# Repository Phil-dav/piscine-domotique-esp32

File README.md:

# Gestion de filtration piscine — ESP32 / Rust

Système domotique embarqué qui pilote la pompe de filtration d'une piscine
familiale : température de l'eau, sécurités matérielles, planification
automatique, tableau de bord web, suivi cloud. Écrit en Rust sur ESP32
(`esp-idf-hal` / `esp-idf-svc`), portage et évolution d'un projet
C++/PlatformIO de référence.

## Sommaire

- [Aperçu](#aperçu)
- [Fonctionnalités](#fonctionnalités)
- [Architecture matérielle](#architecture-matérielle)
- [Organisation des fichiers](#organisation-des-fichiers)
- [Démarrage](#démarrage)
- [Tableau de bord web](#tableau-de-bord-web)
- [État du projet](#état-du-projet)
- [Licence](#licence)

## Aperçu

Le montage pilote une pompe de filtration selon trois modes sélectionnables
par un interrupteur physique — **AUTO** (durée de filtration calculée selon la
température de l'eau, dans une plage horaire configurable), **MANUEL**
(marche/arrêt à la demande) et **OFF** — avec un jeu de sécurités matérielles
(niveau d'eau, défaut moteur, anti-gel, canicule) qui prennent le pas sur
n'importe quel mode en cas de besoin. Un serveur web embarqué directement sur
l'ESP32 sert un tableau de bord en temps réel, sans dépendance à un service
externe pour fonctionner au quotidien.

## Fonctionnalités

- **Trois modes de fonctionnement** (interrupteur physique 3 positions) : AUTO,
  MANUEL (bouton ou page web), OFF.
- **Sécurités matérielles** : niveau d'eau, défaut moteur (disjoncteur),
  anti-gel, canicule, anti-claquement du relais (protection contre un cyclage
  trop rapide).
- **Task Watchdog** : tout blocage de plus de 5 s de la boucle principale
  déclenche un redémarrage automatique et journalisé, plutôt qu'un blocage
  total silencieux.
- **Tableau de bord web embarqué**, servi directement par l'ESP32 : température
  eau/air, humidité, état pompe, mode, position GPS, tension batterie, timeline
  colorée des modes de la journée (avec trace réelle de la marche pompe),
  marche forcée, réglage de la plage horaire, consultation des journaux
  (sessions pompe, bilans journaliers, alertes).
- **Journalisation persistante** (NVS) : sessions pompe, bilans journaliers,
  alertes, et compteurs du jour — survivent aux redémarrages.
- **Suivi cloud** vers [Adafruit IO](https://io.adafruit.com) : envoi groupé de
  toutes les mesures en une seule requête HTTP par cycle, dans un fil
  d'exécution dédié, jamais dans la boucle principale surveillée par le
  watchdog.
- **Horodatage GPS avec repli NTP** : heure fiable même sans réseau Wi-Fi.
- **Suivi de l'alimentation batterie/solaire** (en cours de câblage) : deux
  ponts diviseurs de tension pour surveiller la batterie 12V et la sortie
  régulée 5V d'un contrôleur de charge solaire.

## Architecture matérielle

| Bus / broche | Composant | Rôle |
| --- | --- | --- |
| I2C (GPIO21 SDA, GPIO22 SCL, 400 kHz) | AHT10 (0x38) | Température / humidité air |
| I2C | PCF8574 (0x21) | Expandeur de broches (relais, boutons, interrupteur de mode) |
| I2C | SSD1306 (0x3C) | Écran OLED de diagnostic |
| 1-Wire (GPIO4) | DS18B20 | Température de l'eau |
| UART2 (GPIO16 RX) | Module GPS | Horodatage et coordonnées |
| ADC1 (GPIO34) | Détecteur de niveau | Sécurité niveau d'eau |
| ADC1 (GPIO32, GPIO35) | Ponts diviseurs | Tension batterie 12V / sortie solaire 5V |

Détail du câblage du PCF8574 : P0 pilote le relais pompe, P3 le relais de
défaut système, P4/P5/P6 lisent respectivement le bouton écran et
l'interrupteur de mode (MANU/AUTO), P7 lit le retour de défaut moteur.

Schéma KiCad complet du montage. Il inclut des blocs anticipés dans la
conception (carte micro SD, pH-mètre PH-4502C, interrupteurs de logs série)
qui sont déjà câblés mais **pas encore pris en charge par le firmware
actuel** — schéma établi en amont de la réalisation, comme il est d'usage en
électronique.

Une [version vectorielle au format SVG](https://raw.githubusercontent.com/Phil-dav/piscine-domotique-esp32/main/docs/Gestion%20filtration%20piscine.svg)
est également disponible. Elle s'ouvre en plein écran dans le navigateur et se
zoome avec **Ctrl + molette** sans aucune perte de qualité, ce qui permet de lire
les références et les valeurs de chaque composant.

## Organisation des fichiers

Tout part de `main.rs`, qui orchestre les modules ci-dessous (capteurs, sécurité,
réseau, persistance) à chaque tour de la boucle principale.

```text
src/
├── main.rs             Point d'entrée : boucle principale, initialisation matérielle,
│                        orchestration de tous les modules ci-dessous
├── config.rs            Identifiants et réglages (Wi-Fi, Adafruit IO, broches) — non
│                        suivi par Git, voir config.example.rs pour le modèle
├── config.example.rs    Modèle de config.rs à copier et remplir localement
│
├── Capteurs
│   ├── aht10.rs          Driver du capteur AHT10 (température/humidité air)
│   ├── ds18b20.rs        Driver de la sonde DS18B20 (température eau, 1-Wire)
│   ├── gps.rs            Lecture des trames NMEA du module GPS
│   ├── niveau_eau.rs     Détection du niveau d'eau (sécurité)
│   └── batterie.rs       Lecture des tensions batterie/solaire (ADC)
│
├── Pilotage
│   ├── pcf8574.rs        Pilotage de l'expandeur I2C (relais, boutons, interrupteur)
│   ├── pompe.rs          État de la pompe (marche/arrêt, anti-claquement, compteurs)
│   ├── boost.rs          Marche/arrêt forcée temporaire
│   ├── filtration_auto.rs  Calcul de la durée de filtration (mode AUTO)
│   ├── securite.rs       Détection défaut moteur
│   └── historique_modes.rs  Historique coloré des modes pour la timeline du dashboard
│
├── Stockage et journalisation
│   ├── stockage.rs       Accès générique à la mémoire NVS (clé/valeur)
│   ├── journal.rs        Journaux persistés : sessions pompe, bilans, alertes
│   └── temps.rs          Conversion d'heure (UTC vers Europe/Paris, DST)
│
├── Réseau et interface
│   ├── wifi.rs           Connexion Wi-Fi
│   ├── web_server.rs     Serveur web embarqué : routes HTTP et API du dashboard
│   ├── adafruit_io.rs    Envoi des mesures vers Adafruit IO (cloud)
│   ├── etat_partage.rs   État partagé entre la boucle principale et le serveur web
│   ├── ecran.rs          Affichage sur l'écran OLED de diagnostic
│   ├── index.html        Page du tableau de bord
│   └── script.js         Logique JavaScript du tableau de bord
```

## Démarrage

1. Copier `src/config.example.rs` vers `src/config.rs` et y renseigner tes
   propres identifiants (Wi-Fi, clé Adafruit IO si tu utilises ce service —
   sinon laisse les valeurs par défaut, le programme continue de fonctionner
   sans Wi-Fi ni cloud).
2. Toolchain ESP-IDF `v5.5.3`, cible `xtensa-esp32-espidf` (voir
   `rust-toolchain.toml` et `.cargo/config.toml`).
3. `cargo check` pour vérifier, `cargo run` pour flasher (nécessite
   `espflash`).

## Tableau de bord web

Servi directement par l'ESP32 sur le réseau local (pas de service externe
requis) : mesures en temps réel, contrôle de la pompe et du mode, timeline
colorée de la journée, historique des sessions/alertes, réglage de la plage
de filtration.

## État du projet

En développement actif — les fonctionnalités listées ci-dessus sont
opérationnelles et testées en conditions réelles. Chantiers en cours ou à
venir : carte SD pour un historique complet, capteur de courant sur
l'alimentation pompe, alarme de température du coffret électrique, alertes
push (ntfy.sh).

## Licence

Projet personnel, à but pédagogique et domestique.

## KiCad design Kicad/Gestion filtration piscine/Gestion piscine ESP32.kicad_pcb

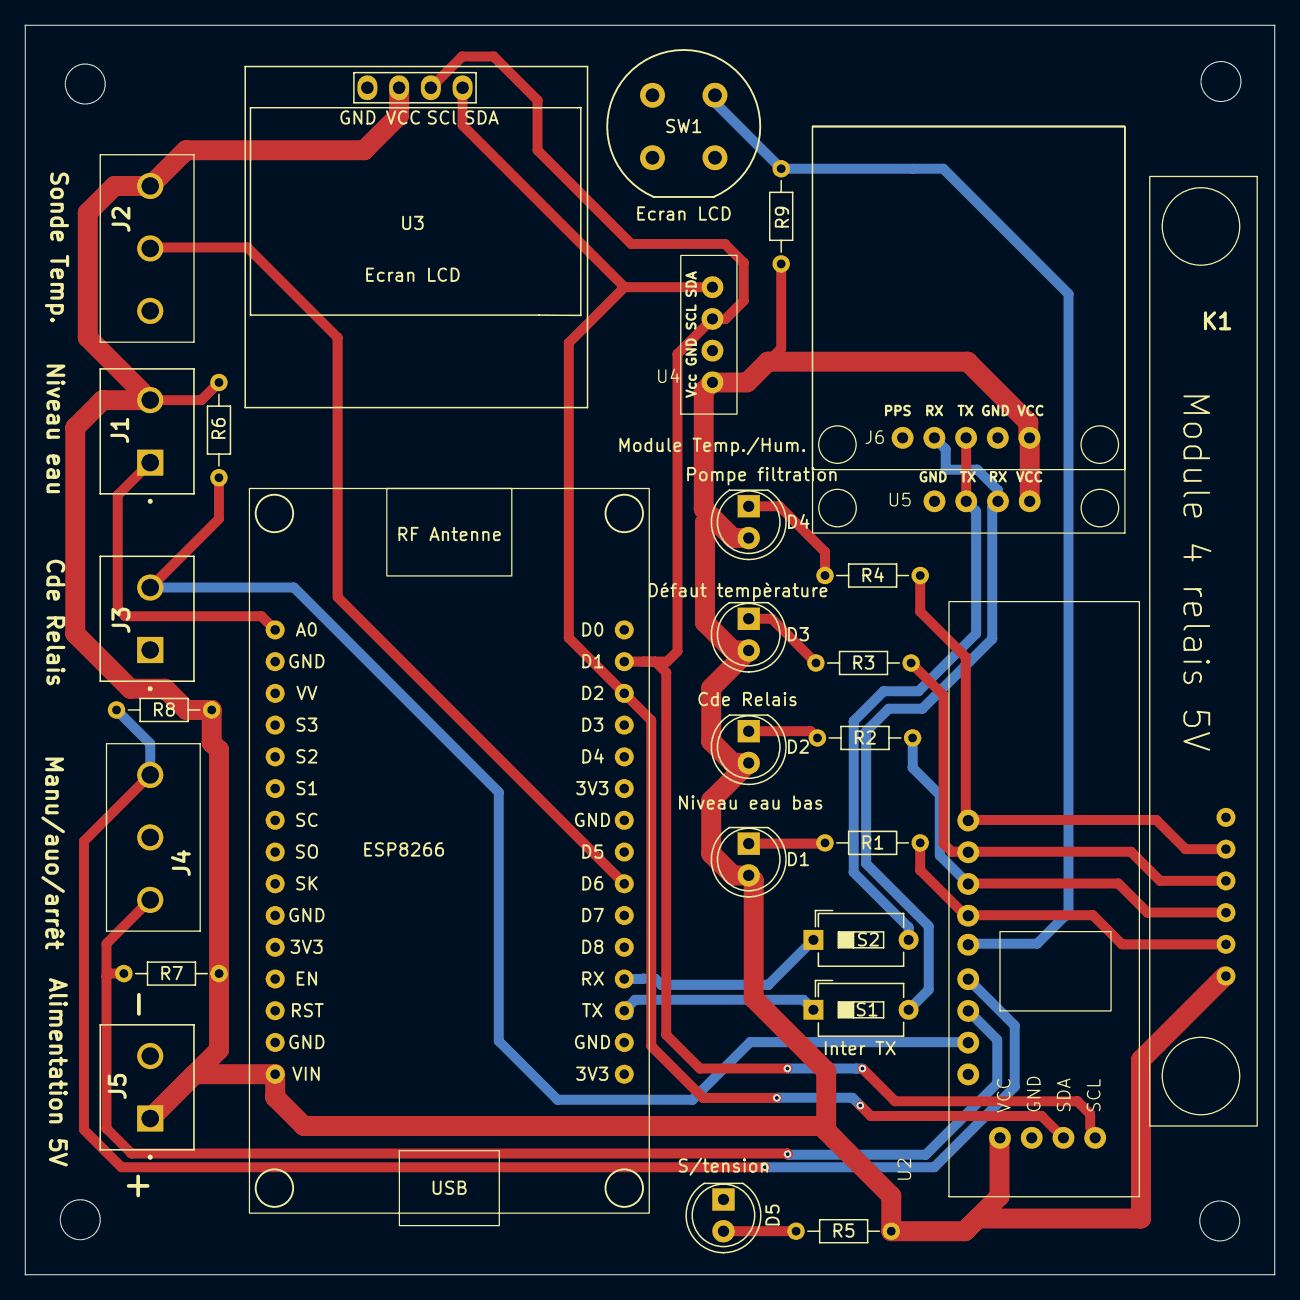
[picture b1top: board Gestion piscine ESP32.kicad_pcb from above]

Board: 2 copper layers, 100.0 x 100.0 mm, 29 parts (0 on the bottom side), 23 nets.

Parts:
D1: Niveau eau bas; LED_D5.0mm_IRGrey
D2: Cde Relais; LED_D5.0mm_IRGrey
D3: Défaut tempèrature; LED_D5.0mm_IRGrey
D4: Pompe filtration; LED_D5.0mm_IRGrey
D5: S/tension; LED_D5.0mm_IRGrey
J1: Niveau eau; KF301-2P
J2: Sonde Temp.; KF301-3P
J3: Cde Relais; KF301-2P
J4: Manu/auo/arrêt; KF301-3P
J5: Alimentation 5V; KF301-2P
J6: GPS 6M2; GPS-6MV2
K1: HL-54S; HL-54S V1.0
R1, R2, R3, R4, R9: 330; R_Axial_DIN0204_L3.6mm_D1.6mm_P7.62mm_Horizontal
R5, R6, R7, R8: 10k; R_Axial_DIN0204_L3.6mm_D1.6mm_P7.62mm_Horizontal
S1: Inter TX; SW_DIP_SPSTx01_Slide_6.7x4.1mm_W7.62mm_P2.54mm_LowProfile
S2: inter RX; SW_DIP_SPSTx01_Slide_6.7x4.1mm_W7.62mm_P2.54mm_LowProfile
SW1: Ecran LCD; Push_E-Switch_KS01Q01
U1: ESP8266; ESP8266_NodeMCU
U2: PCF8574
U3: Ecran LCD; 128x64OLED
U4: Module Temp./Hum.; AHT10
U5: Module GPS; GY-GPS-6MV2

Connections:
GND: D5.1 (K), J2.1, J3.1, J4.2, J5.2, J6.2, K1.1 (GND), SW1.1, U1.2 (GND), U1.10 (GND), U1.14 (GND), U1.17 (GND), U1.24 (GND), U2.8 (GND), U3.1 (GND), U4.2 (GND), U5.4 (GND)
unnamed: D1.1 (K), R1.1
unnamed: D2.1 (K), R2.1
unnamed: D3.1 (K), R3.1
unnamed: D4.1 (K), R4.1
unnamed: D5.2 (A), R9.2
unnamed: J6.3, S2.2, U5.3 (TX)
unnamed: J6.4, S1.2, U5.2 (RX)
unnamed: K1.2 (IN1), R4.2, U2.4 (P0)
unnamed: K1.3 (IN2), R3.2, U2.5 (P1)
unnamed: K1.4 (IN3), R2.2, U2.6 (P2)
unnamed: K1.5 (IN4), R1.2, U2.7 (P3)
unnamed: R8.1, SW1.2, U2.9 (P4)
unnamed: J4.1, R7.1, U2.10 (P5)
unnamed: J4.3, R6.1, U2.11 (P6)
unnamed: J3.2, R5.1, U2.12 (P7)
Niveau Eau: J1.1, U1.1 (A0)
RX: S2.1, U1.19 (RX)
SCL: U1.29 (D1), U2.14 (SCL), U3.3 (SCL), U4.3 (SCL)
SDA: U1.28 (D2), U2.15 (SDA), U3.4 (SDA), U4.4 (SDA)
TX: S1.1, U1.18 (TX)
Temp. Eau: J2.2, U1.22 (D6)
VCC: D1.2 (A), D2.2 (A), D3.2 (A), D4.2 (A), J1.2, J2.3, J5.1, J6.1, K1.6 (VCC), R5.2, R6.2, R7.2, R8.2, R9.1, U1.15 (VIN), U2.16 (VCC), U3.2 (VCC), U4.1 (VCC), U5.1 (VCC)

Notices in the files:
README.md:
License: projet personnel
